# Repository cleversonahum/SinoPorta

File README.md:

# SinoPorta
Para rodar a aplicação é necessário que o servidor em Node seja iniciado. O arquivo é "server.js" que esta na pasta "server" (antes use o 'npm install' para instalar as dependências necessárias).
Após isso basta rodar "ionic serve" na pasta raiz do projeto.

Obs: É necessário que o Ionic e o Node js estejam devidamente instalados.

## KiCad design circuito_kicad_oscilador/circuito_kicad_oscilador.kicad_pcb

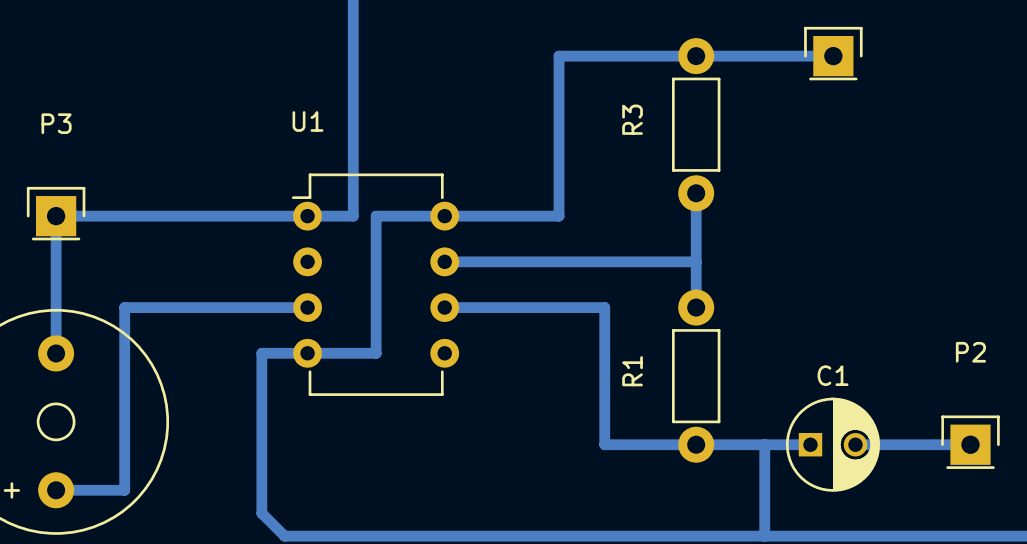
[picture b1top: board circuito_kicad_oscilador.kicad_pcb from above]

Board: 2 copper layers, 8 parts (0 on the bottom side), 5 nets.

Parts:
C1: CAP; C_Radial_D5_L6_P2.5
P1: 1 - CONN_01X01; Pin_Header_Straight_1x01
P2: 2 - CONN_01X01; Pin_Header_Straight_1x01
P3: 3 - CONN_01X01; Pin_Header_Straight_1x01
R1, R3: R; Resistor_Horizontal_RM7mm
SP1: Buzzer AL11P; Buzzer_12x9.5RM7.6
U1: TLC555; DIP-8_W7.62mm

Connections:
unnamed: C1.1, R3.2, U1.2, U1.6
unnamed: C1.2, P2.1
unnamed: P1.1, R1.1, U1.4, U1.8
unnamed: P3.1, U1.1
unnamed: R1.2, R3.1, U1.7

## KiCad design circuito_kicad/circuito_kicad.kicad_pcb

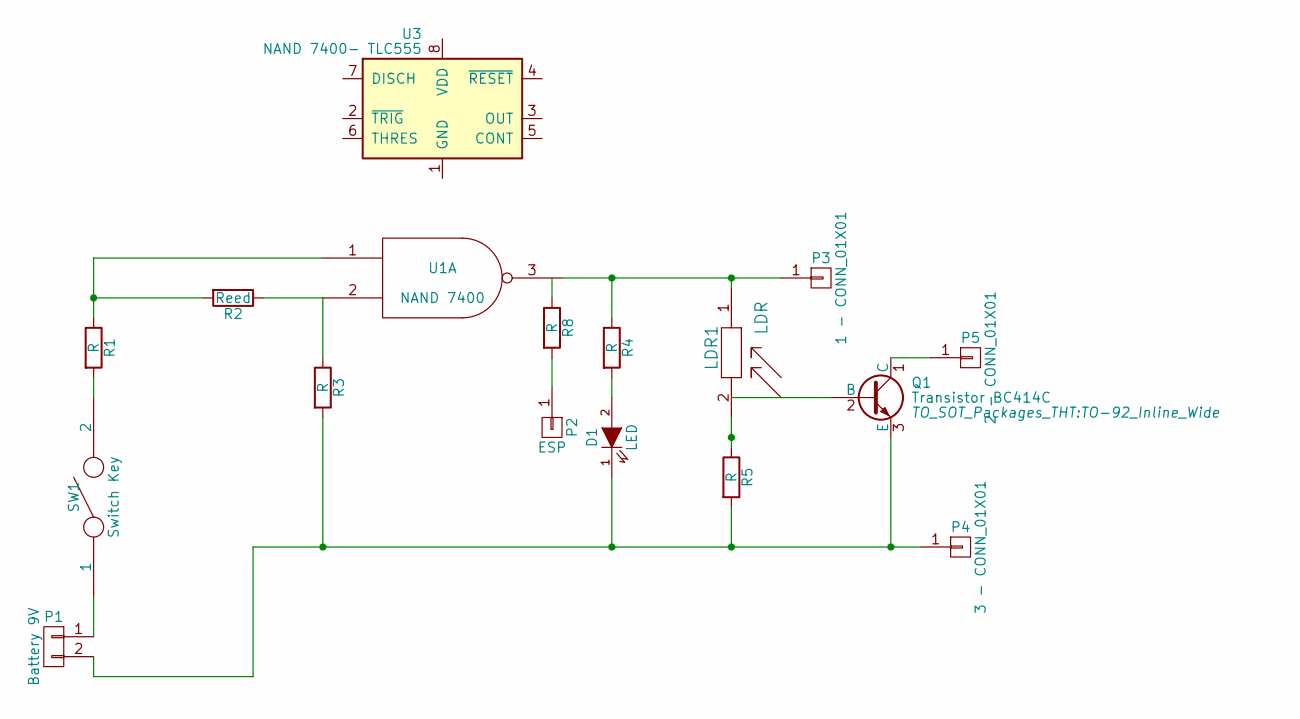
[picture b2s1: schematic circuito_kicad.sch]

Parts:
D1: LED; LED-5MM
LDR1: LDR; Resistor_Horizontal_RM7mm
P1: Battery 9V; Pin_Header_Straight_1x02
P2: ESP; Pin_Header_Straight_1x01
P3: 1 - CONN_01X01; Pin_Header_Straight_1x01
P4: 3 - CONN_01X01; Pin_Header_Straight_1x01
P5: 2 - CONN_01X01; Pin_Header_Straight_1x01
Q1: Transistor BC414C; TO-92_Inline_Wide
R1, R3, R4, R5, R8: R; Resistor_Horizontal_RM7mm
R2: Reed; Resistor_Horizontal_RM7mm
SW1: Switch Key; SW_DIP_x1_Slide
U1: NAND 7400
U3: NAND 7400- TLC555; DIP-14_W7.62mm

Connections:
unnamed: D1.1 (K), P1.2, P4.1, Q1.3 (E), R3.2, R5.2
unnamed: D1.2 (A), R4.2
unnamed: LDR1.1, P3.1, R4.1, U1.3
unnamed: LDR1.2, R5.1
unnamed: P1.1, SW1.1
unnamed: P2.1, R8.2
unnamed: P5.1, Q1.1 (C)
unnamed: R1.1, R2.2, U1.1
unnamed: R1.2, SW1.2
unnamed: R2.1, R3.1, U1.2

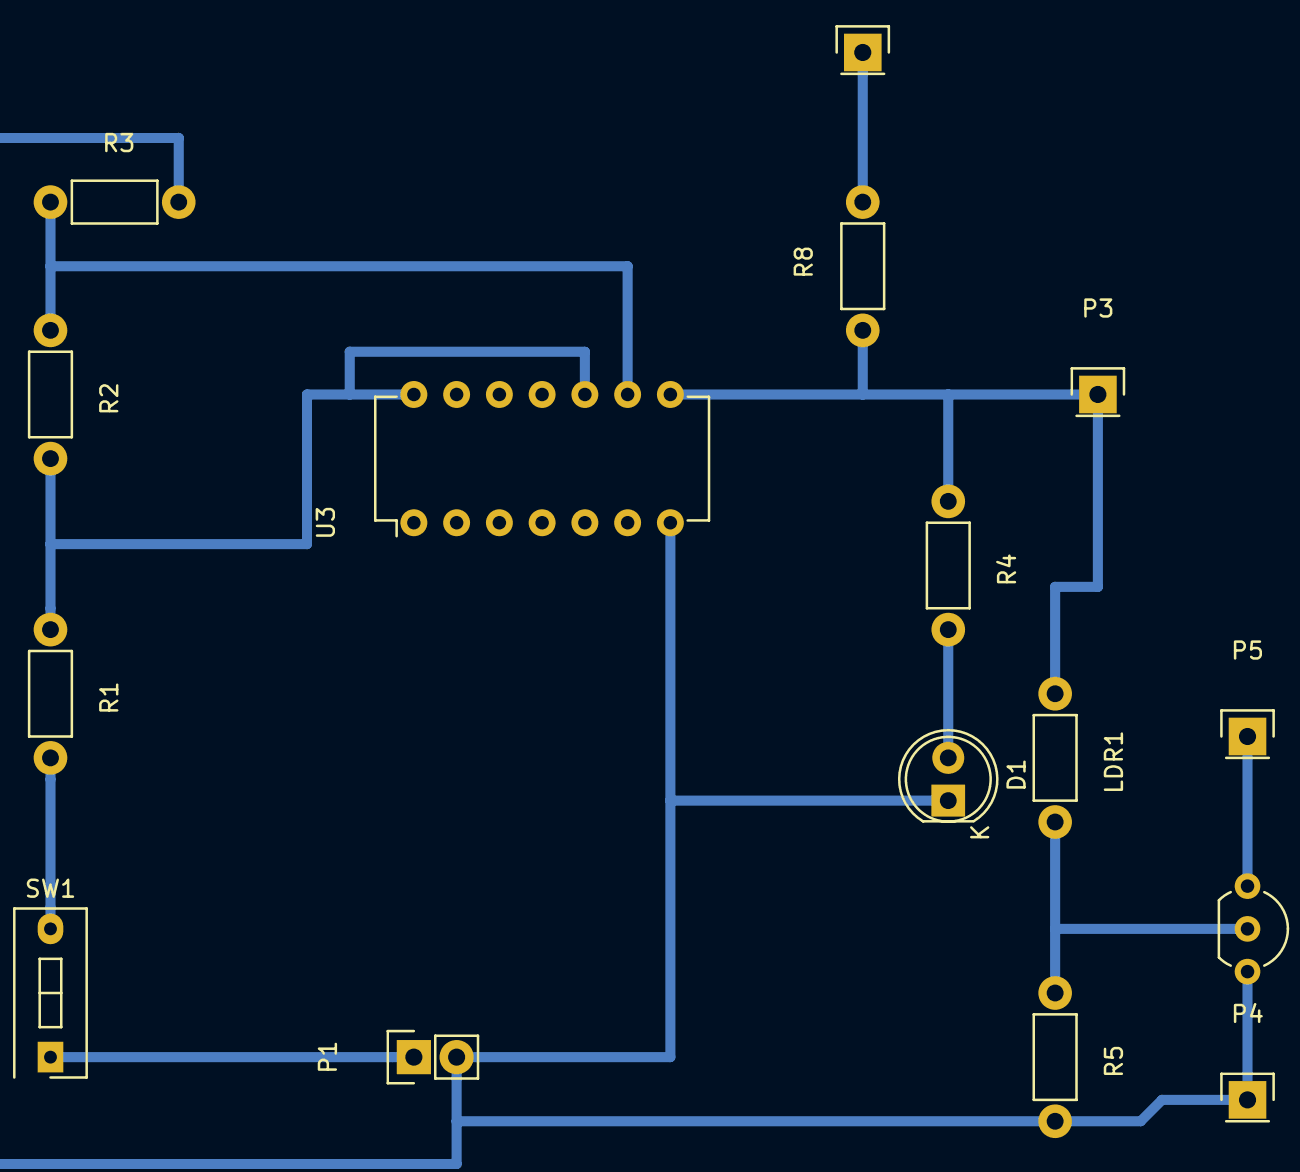
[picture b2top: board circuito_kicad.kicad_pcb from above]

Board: 2 copper layers, 16 parts (0 on the bottom side), 10 nets.

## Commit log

2016-08-15 the inittial project
2016-08-28 App funcionando
2016-09-24 Placas Kicad Prontas (placa oscilador e principal)
2016-09-24 Placas adicionadas
2016-09-24 modificação controller
